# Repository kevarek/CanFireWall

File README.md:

# CanFireWall
Invisible pass-through device for CAN bus to secretly log, filter and alter communication.

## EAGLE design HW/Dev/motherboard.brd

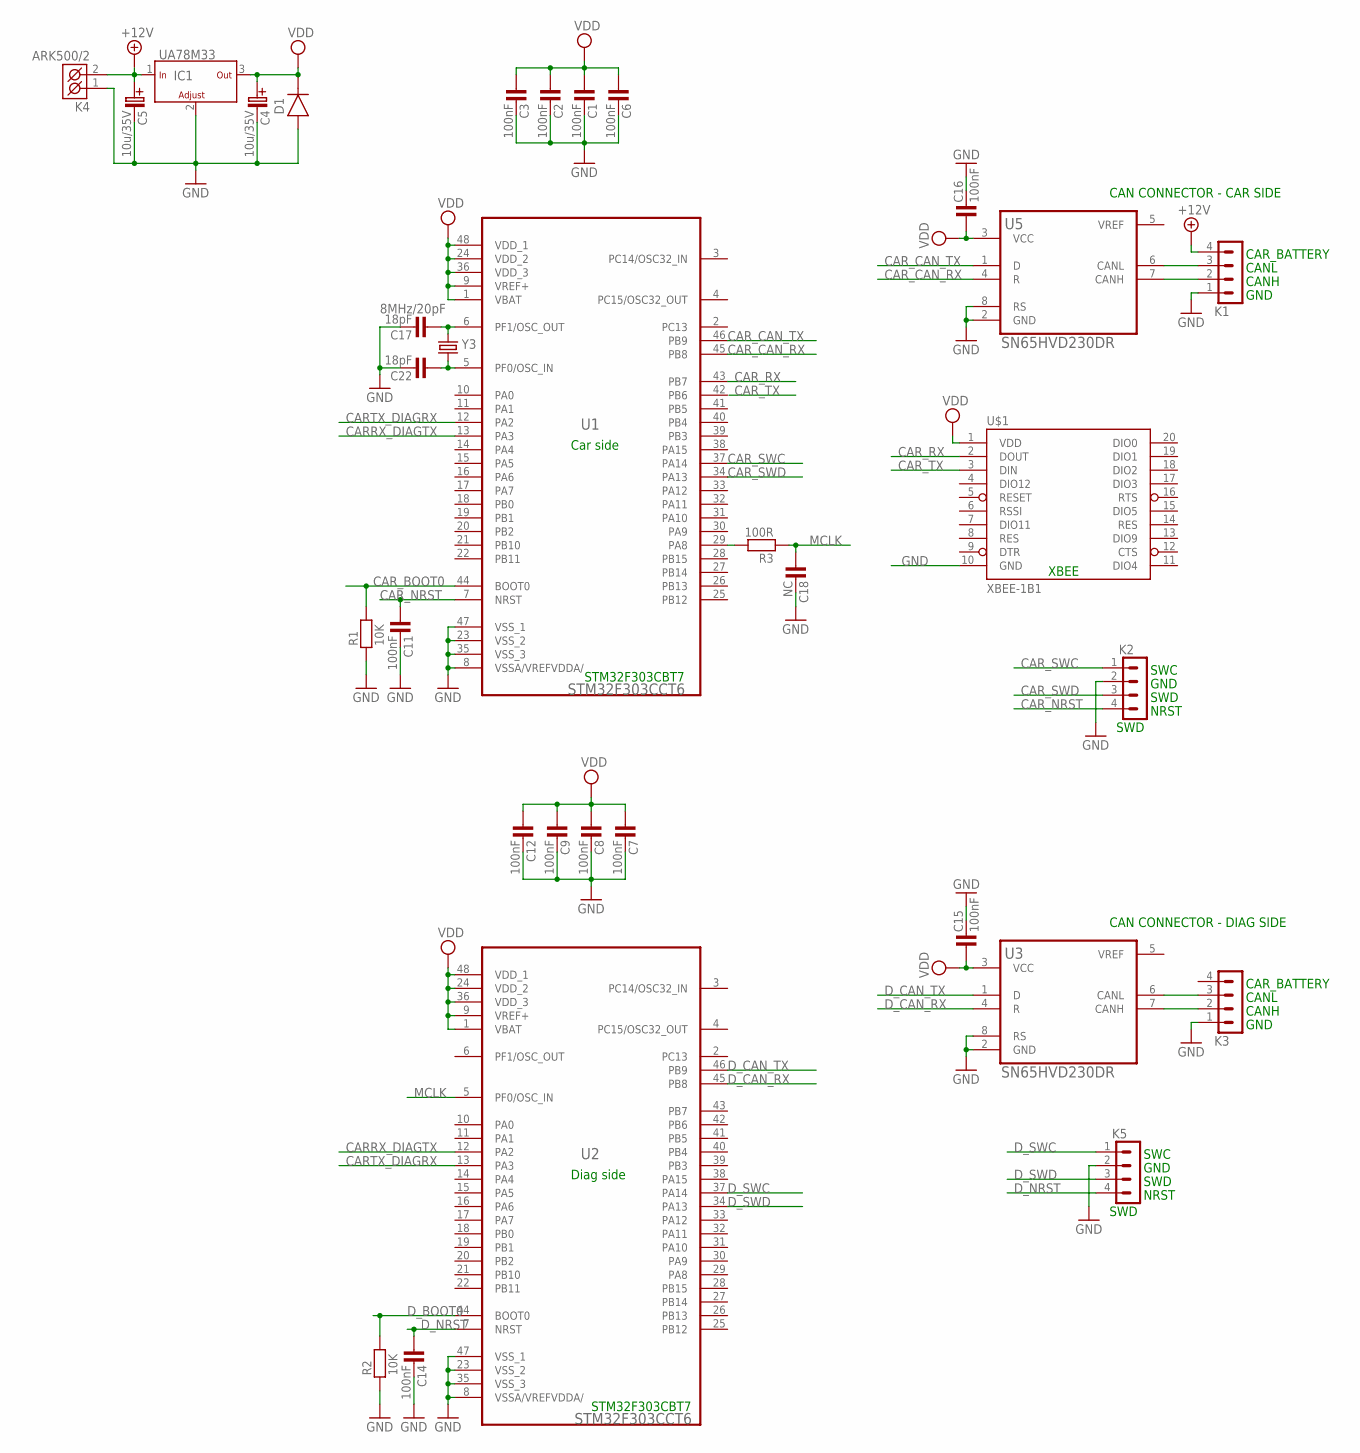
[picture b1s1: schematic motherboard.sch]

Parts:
C1, C2, C3, C6, C7, C8, C9, C11, C12, C14, C15, C16: 100nF; 0805
C4, C5: 10u/35V; C-EL_2,5
C17, C22: 18pF; 1206
C18: NC; 0805
D1: 1N4007SMD; MELF
IC1: UA78M33; TO285P991X230-3N
K1, K2, K3, K5: PSH02-04P
K4: ARK500/2
R1, R2: 10K; 0805
R3: 100R; 0805
U1, U2: STM32F303CCT6; QFP50P900X900X160-48N
U3, U5: SN65HVD230DR; SOIC127P600X175-8N
U$1: XBEE-1B1; XBEE-1
Y3: 8MHz/20pF; HC49UP

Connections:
+12V: C5.C+ (C_EL+), IC1.1 (IN), K1.4, K4.2 (K2)
CARRX_DIAGTX: U1.13 (PA3), U2.12 (PA2)
CARTX_DIAGRX: U1.12 (PA2), U2.13 (PA3)
CAR_BOOT0: R1.2, U1.44 (BOOT0)
CAR_CAN_RX: U1.45 (PB8), U5.4 (R)
CAR_CAN_TX: U1.46 (PB9), U5.1 (D)
CAR_NRST: C11.1, K2.4, U1.7 (NRST)
CAR_RX: U1.43 (PB7), U$1.2 (DOUT)
CAR_SWC: K2.1, U1.37 (PA14)
CAR_SWD: K2.3, U1.34 (PA13)
CAR_TX: U$1.3 (DIN)
D_BOOT0: R2.2, U2.44 (BOOT0)
D_CAN_RX: U2.45 (PB8), U3.4 (R)
D_CAN_TX: U2.46 (PB9), U3.1 (D)
D_NRST: C14.1, K5.4, U2.7 (NRST)
D_SWC: K5.1, U2.37 (PA14)
D_SWD: K5.3, U2.34 (PA13)
GND: C1.2, C2.2, C3.2, C4.C- (C_EL-), C5.C- (C_EL-), C6.2, C7.2, C8.2, C9.2, C11.2, C12.2, C14.2, C15.2, C16.2, C17.2, C18.2, C22.2, D1.A, IC1.2 (ADJ), K1.1, K2.2, K3.1, K4.1 (K1), K5.2, R1.1, R2.1, U1.8 (VSSA/VREFVDDA/), U1.23 (VSS_2), U1.35 (VSS_3), U1.47 (VSS_1), U2.8 (VSSA/VREFVDDA/), U2.23 (VSS_2), U2.35 (VSS_3), U2.47 (VSS_1), U3.2 (GND), U3.8 (RS), U5.2 (GND), U5.8 (RS), U$1.10 (GND)
MCLK: C18.1, R3.1, U2.5 (PF0/OSC_IN)
unnamed: K3.2, U3.7 (CANH)
unnamed: K3.3, U3.6 (CANL)
unnamed: R3.2, U1.29 (PA8)
unnamed: K1.2, U5.7 (CANH)
unnamed: K1.3, U5.6 (CANL)
unnamed: C17.1, U1.6 (PF1/OSC_OUT), Y3.2
unnamed: C22.1, U1.5 (PF0/OSC_IN), Y3.1
VDD: C1.1, C2.1, C3.1, C4.C+ (C_EL+), C6.1, C7.1, C8.1, C9.1, C12.1, C15.1, C16.1, D1.K, IC1.3 (OUT), U1.1 (VBAT), U1.9 (VREF+), U1.24 (VDD_2), U1.36 (VDD_3), U1.48 (VDD_1), U2.1 (VBAT), U2.9 (VREF+), U2.24 (VDD_2), U2.36 (VDD_3), U2.48 (VDD_1), U3.3 (VCC), U5.3 (VCC), U$1.1 (VDD)

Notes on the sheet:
STM32F303CBT7
XBEE
Car side
SWD
NRST
SWC
GND
CAR_BATTERY
CANH
CANL
Diag side
CAN CONNECTOR - DIAG SIDE
CAN CONNECTOR - CAR SIDE

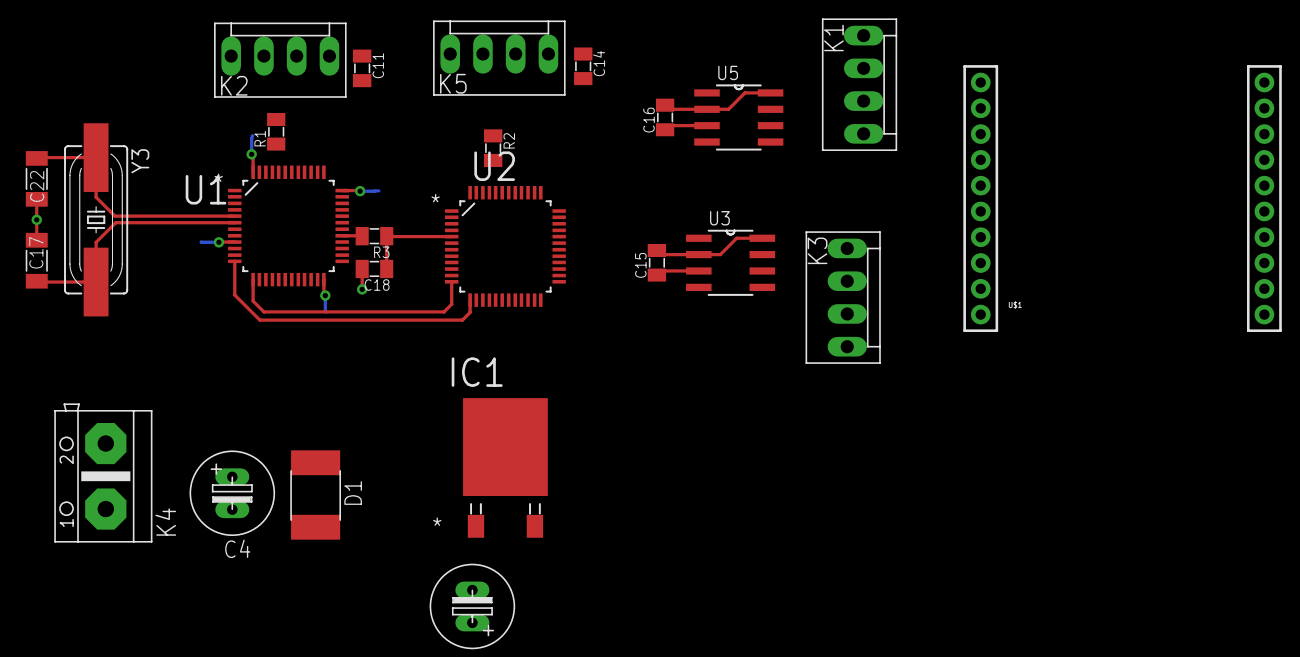
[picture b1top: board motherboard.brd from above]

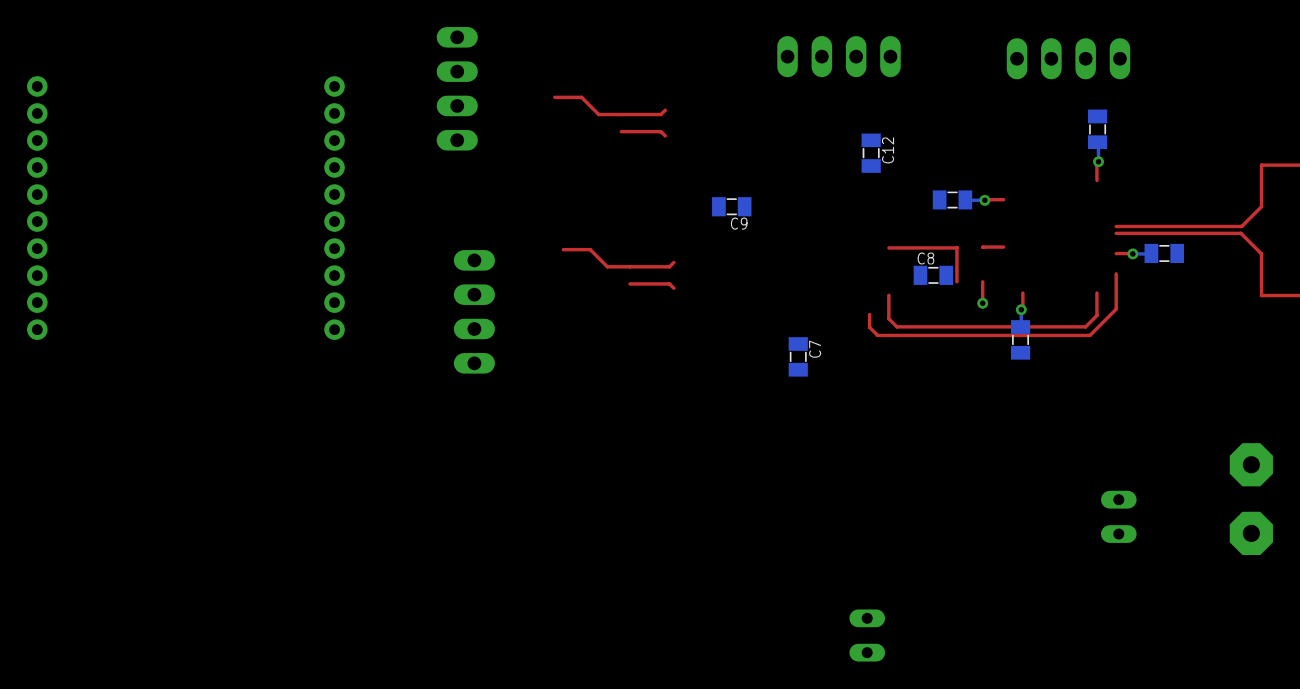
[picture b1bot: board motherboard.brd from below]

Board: 2 copper layers, 33 parts (8 on the bottom side), 26 nets.

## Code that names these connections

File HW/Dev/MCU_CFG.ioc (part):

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Mcu.Name=STM32F303C(6-8)Tx
Mcu.Package=LQFP48
Mcu.UserName=STM32F303C6Tx
PA13.Mode=Serial-Wire
PA13.Signal=SYS_JTMS-SWDIO
PA14.Mode=Serial-Wire
PA14.Signal=SYS_JTCK-SWCLK
PA2.Mode=Asynchronous
PA2.Signal=USART2_TX
PA3.Mode=Asynchronous
PA3.Signal=USART2_RX
PA8.Mode=Clock-out
PA8.Signal=RCC_MCO
PB6.Mode=Asynchronous
PB6.Signal=USART1_TX
PB7.Mode=Asynchronous
PB7.Signal=USART1_RX
PB8.Mode=Master
PB8.Signal=CAN_RX
PB9.Mode=Master
PB9.Signal=CAN_TX
PF0\ /\ OSC_IN.Mode=HSE-External-Oscillator
PF0\ /\ OSC_IN.Signal=RCC_OSC_IN
PF1\ /\ OSC_OUT.Mode=HSE-External-Oscillator
PF1\ /\ OSC_OUT.Signal=RCC_OSC_OUT
RCC.HSE_VALUE=8000000

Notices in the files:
parts and their libraries:
SparkFun: Licensing: CC v3.0 Share-Alike You are welcome to use this library for commercial purposes.
Copyright (C) PaJa 2011
Copyright (C) PaJa 2001-2011
